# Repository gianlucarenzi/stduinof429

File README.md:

# STDuinoF429
=====================================

First attempt to have an ARDUINO (STM32 Based) Board for usage in 8-bit micros
like Atari 400/800/800XL/130XE and Commodore 64

# Rendered Images
# 
# 
# 

Hardware License
---------------------------
Copyright (C) 2018/2019 Gianluca Renzi <gianlucarenzi@eurek.it> <icjtqr@gmail.com>

The hardware of this project is released as free/open hardware under the
GNU GPL v3 License terms. See LICENSE for details.

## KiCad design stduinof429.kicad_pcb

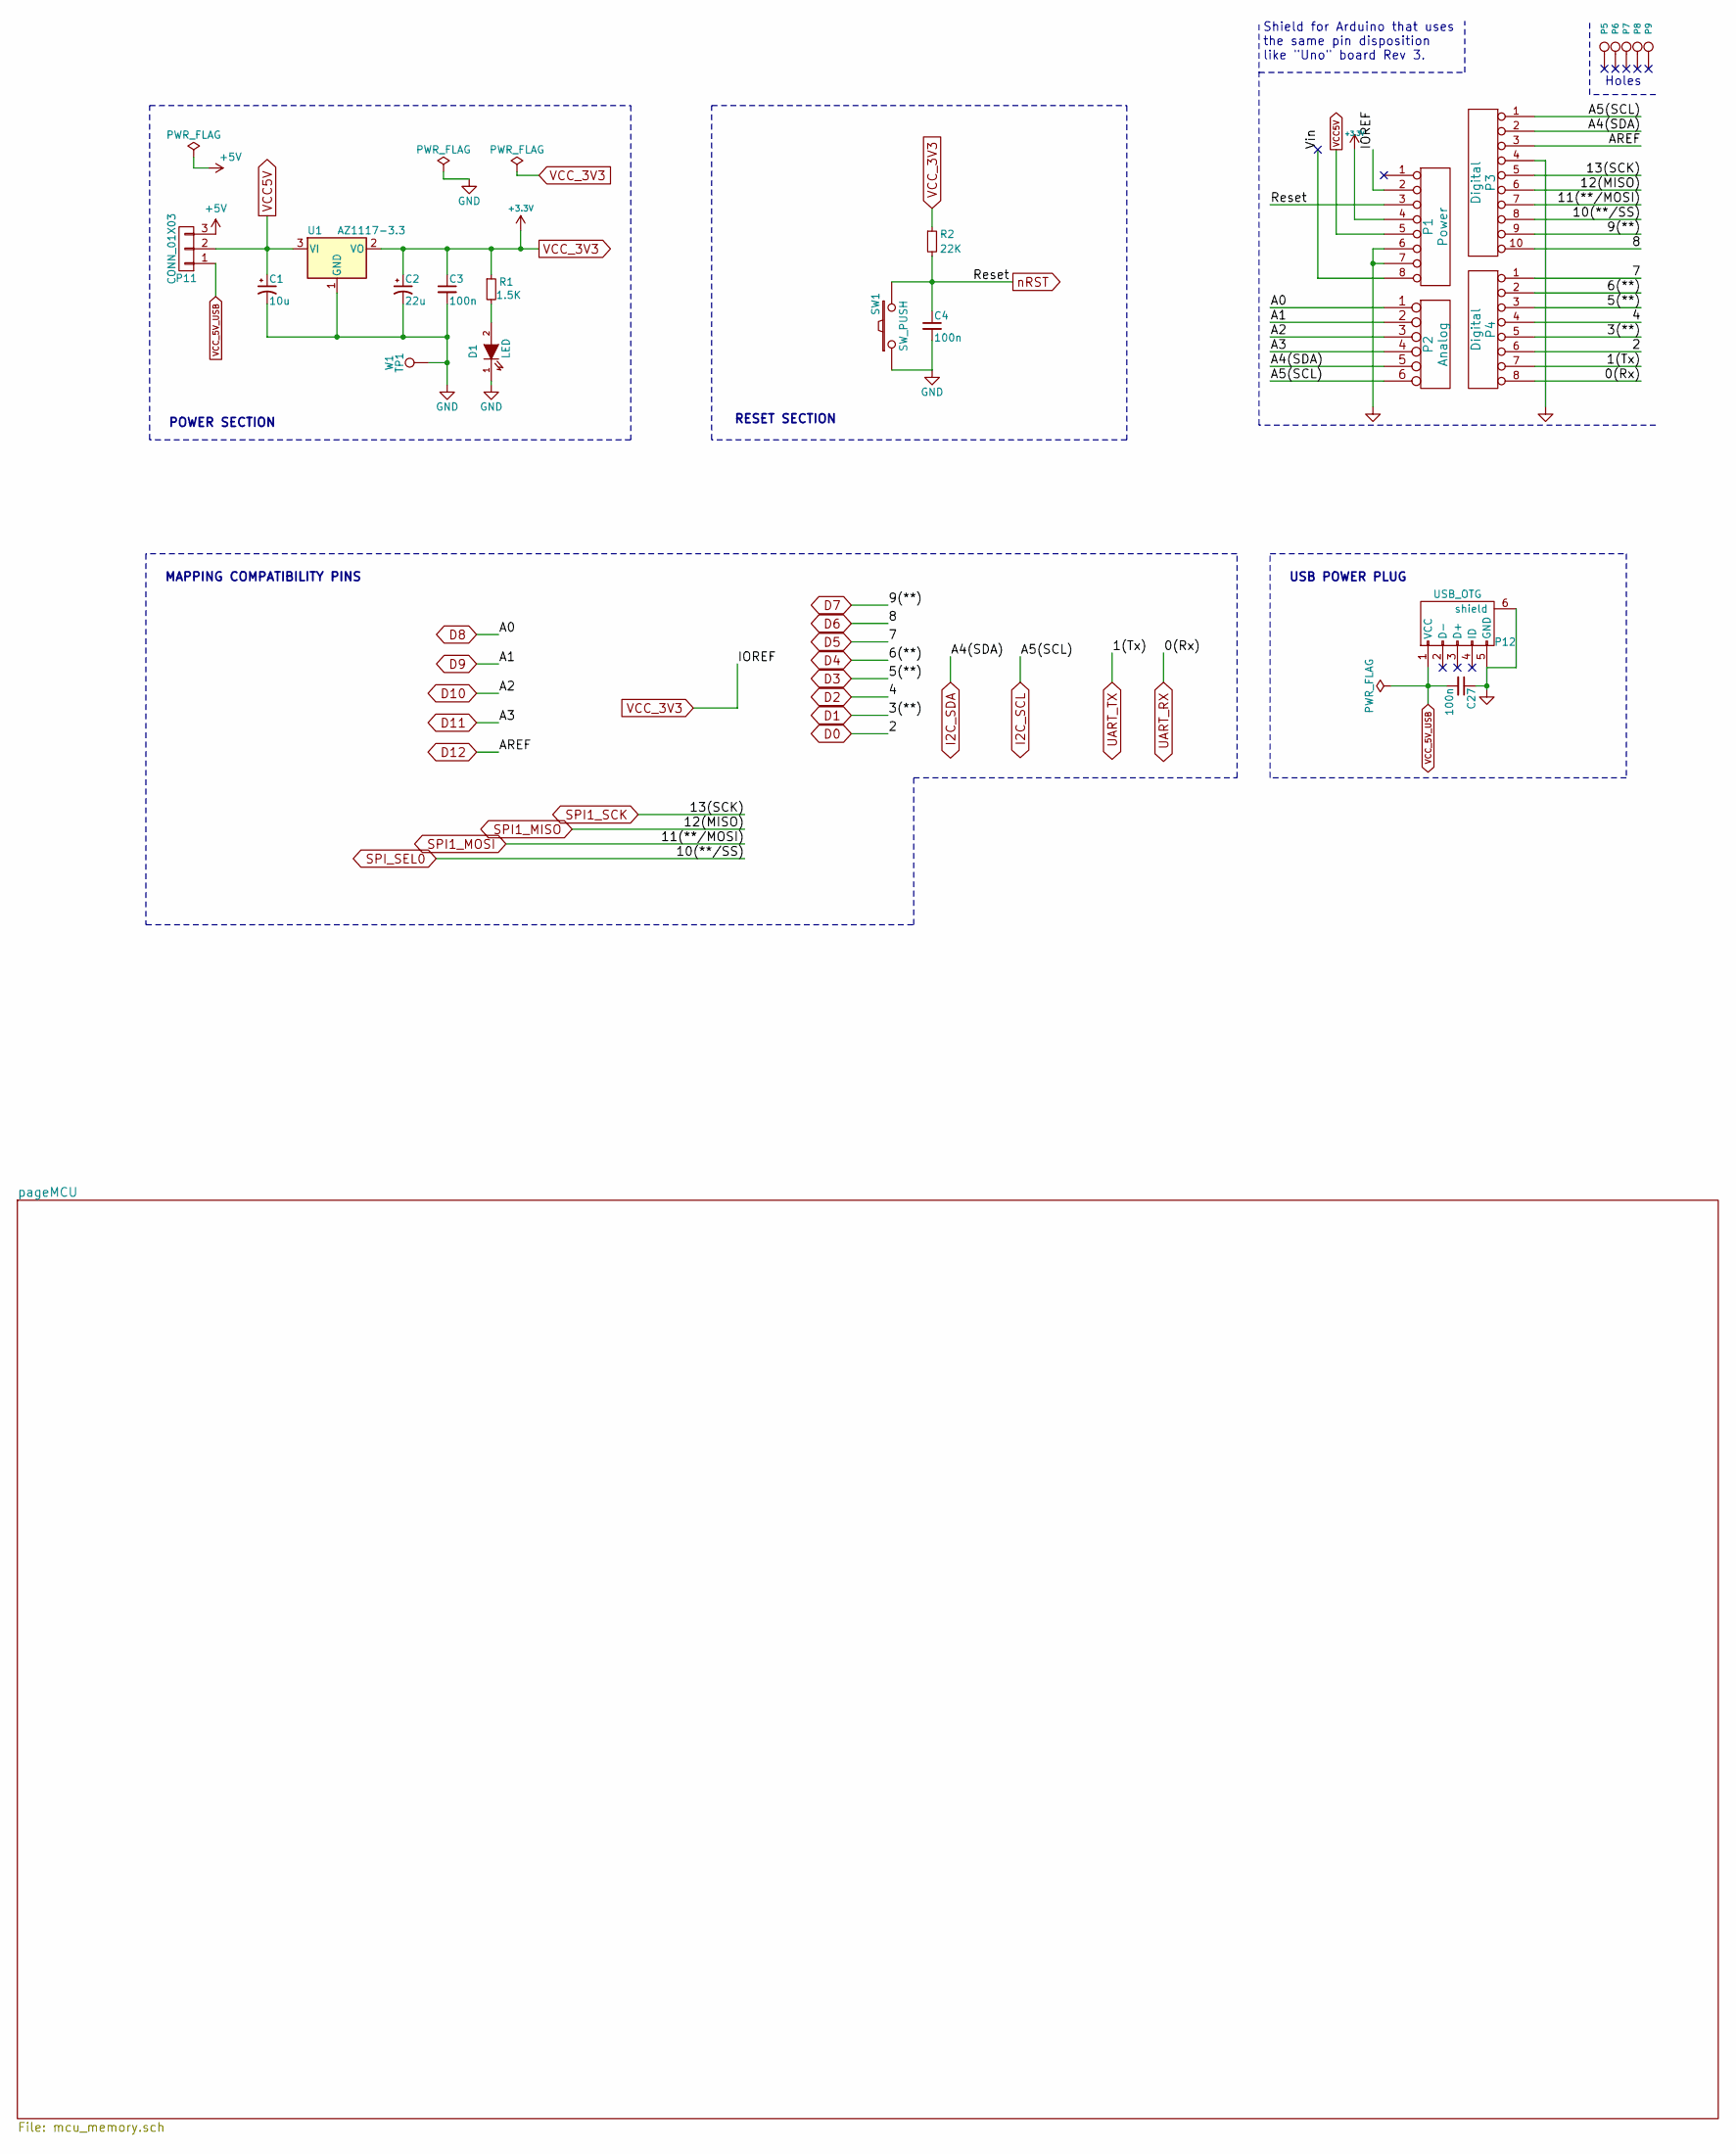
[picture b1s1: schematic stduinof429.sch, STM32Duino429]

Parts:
C1: 10u; CP_EIA-3216-18_Kemet-A_Pad1.58x1.35mm_HandSolder
C2: 22u; CP_EIA-3216-18_Kemet-A_Pad1.58x1.35mm_HandSolder
C3, C4, C27: 100n; C_1210_3225Metric_Pad1.42x2.65mm_HandSolder
D1: LED; LED_1206_3216Metric_Pad1.42x1.75mm_HandSolder
P1: Power; PinSocket_1x08_P2.54mm_Vertical
P2: Analog; PinSocket_1x06_P2.54mm_Vertical
P3: Digital; PinSocket_1x10_P2.54mm_Vertical
P4: Digital; PinSocket_1x08_P2.54mm_Vertical
P5, P6, P7, P8, P9: CONN_1; MountingHole
P11: CONN_01X03; PinHeader_1x03_P2.54mm_Vertical
P12: USB_OTG; USB_Micro-B_Large_Pads
R1: 1.5K; R_1210_3225Metric_Pad1.42x2.65mm_HandSolder
R2: 22K; R_1210_3225Metric_Pad1.42x2.65mm_HandSolder
SW1: SW_PUSH; SW_SPST_FSMSM_3D
U1: AZ1117-3.3; SOT-223
W1: TP1; TestPoint_Pad_D2.0mm

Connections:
+5V: P11.3; also elsewhere on the board
/Vin: P1.8
D0: P4.6; also elsewhere on the board
D1: P4.5; also elsewhere on the board
D2: P4.4; also elsewhere on the board
D3: P4.3; also elsewhere on the board
D4: P4.2; also elsewhere on the board
D5: P4.1; also elsewhere on the board
D6: P3.10; also elsewhere on the board
D7: P3.9; also elsewhere on the board
D8: P2.1; also elsewhere on the board
D9: P2.2; also elsewhere on the board
D10: P2.3; also elsewhere on the board
D11: P2.4; also elsewhere on the board
D12: P3.3; also elsewhere on the board
GND: C1.2, C2.2, C3.2, C4.2, C27.1, D1.1 (K), P1.6, P1.7, P3.4, P12.5 (GND), P12.6 (shield), SW1.1, U1.1 (GND), W1.1; also elsewhere on the board
I2C_SCL: P2.6, P3.1; also elsewhere on the board
I2C_SDA: P2.5, P3.2; also elsewhere on the board
unnamed: D1.2 (A), R1.2
SPI1_MISO: P3.6; also elsewhere on the board
SPI1_MOSI: P3.7; also elsewhere on the board
SPI1_SCK: P3.5; also elsewhere on the board
SPI_SEL0: P3.8; also elsewhere on the board
UART_RX: P4.8; also elsewhere on the board
UART_TX: P4.7; also elsewhere on the board
VCC5V: C1.1, P1.5, P11.2, U1.3 (VI); also elsewhere on the board
VCC_3V3: C2.1, C3.1, P1.2, P1.4, R1.1, R2.1, U1.2 (VO); also elsewhere on the board
VCC_5V_USB: C27.2, P11.1, P12.1 (VCC)
nRST: C4.1, P1.3, R2.2, SW1.2; also elsewhere on the board

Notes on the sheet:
Holes
Shield for Arduino that uses the same pin disposition like "Uno" board Rev 3.
POWER SECTION
MAPPING COMPATIBILITY PINS
RESET SECTION
USB POWER PLUG

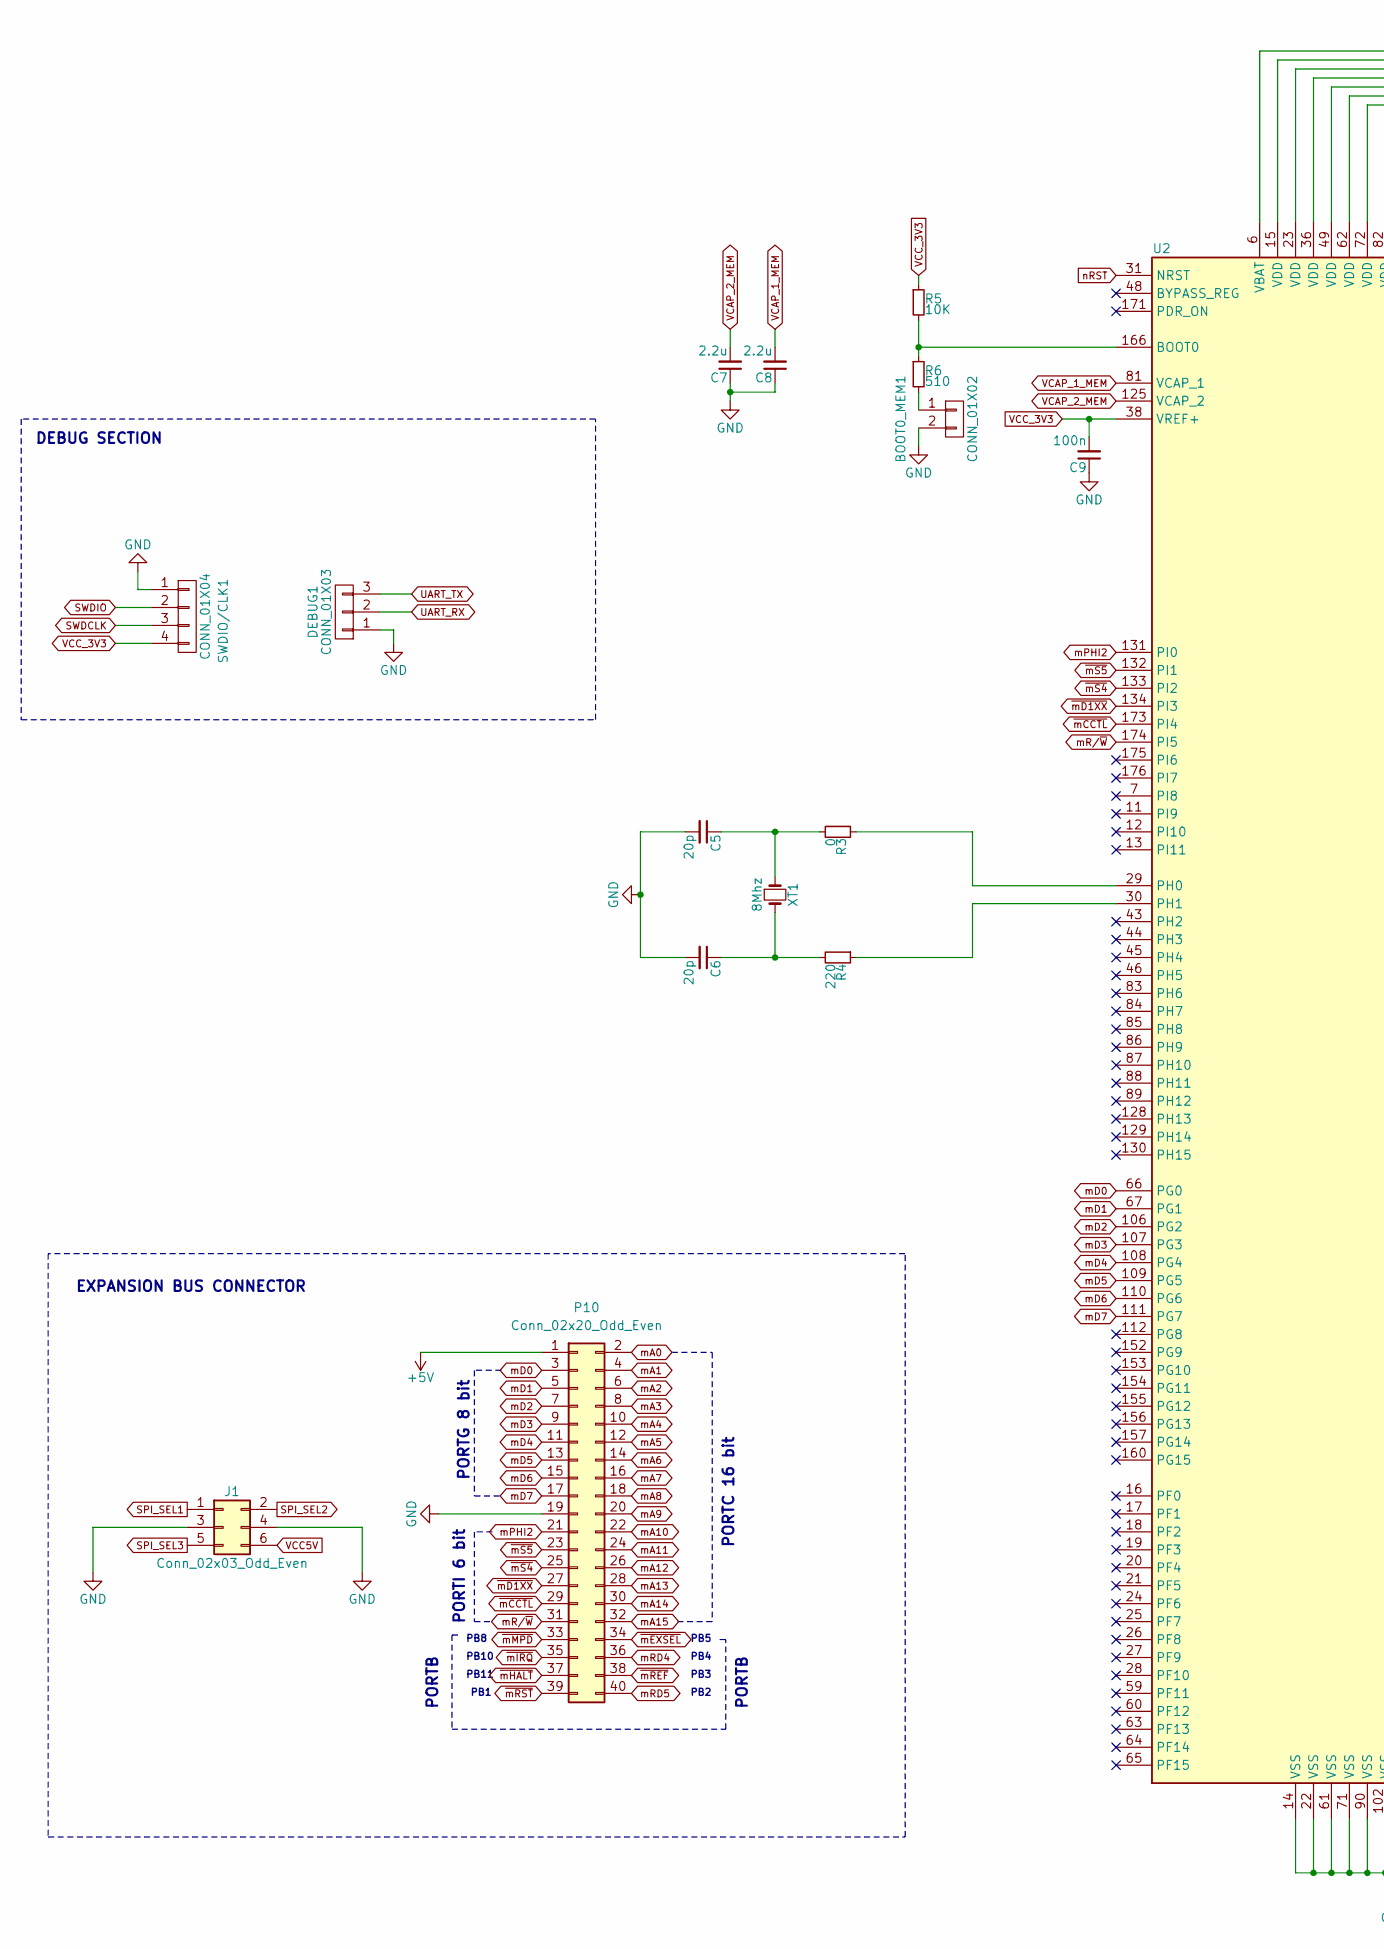
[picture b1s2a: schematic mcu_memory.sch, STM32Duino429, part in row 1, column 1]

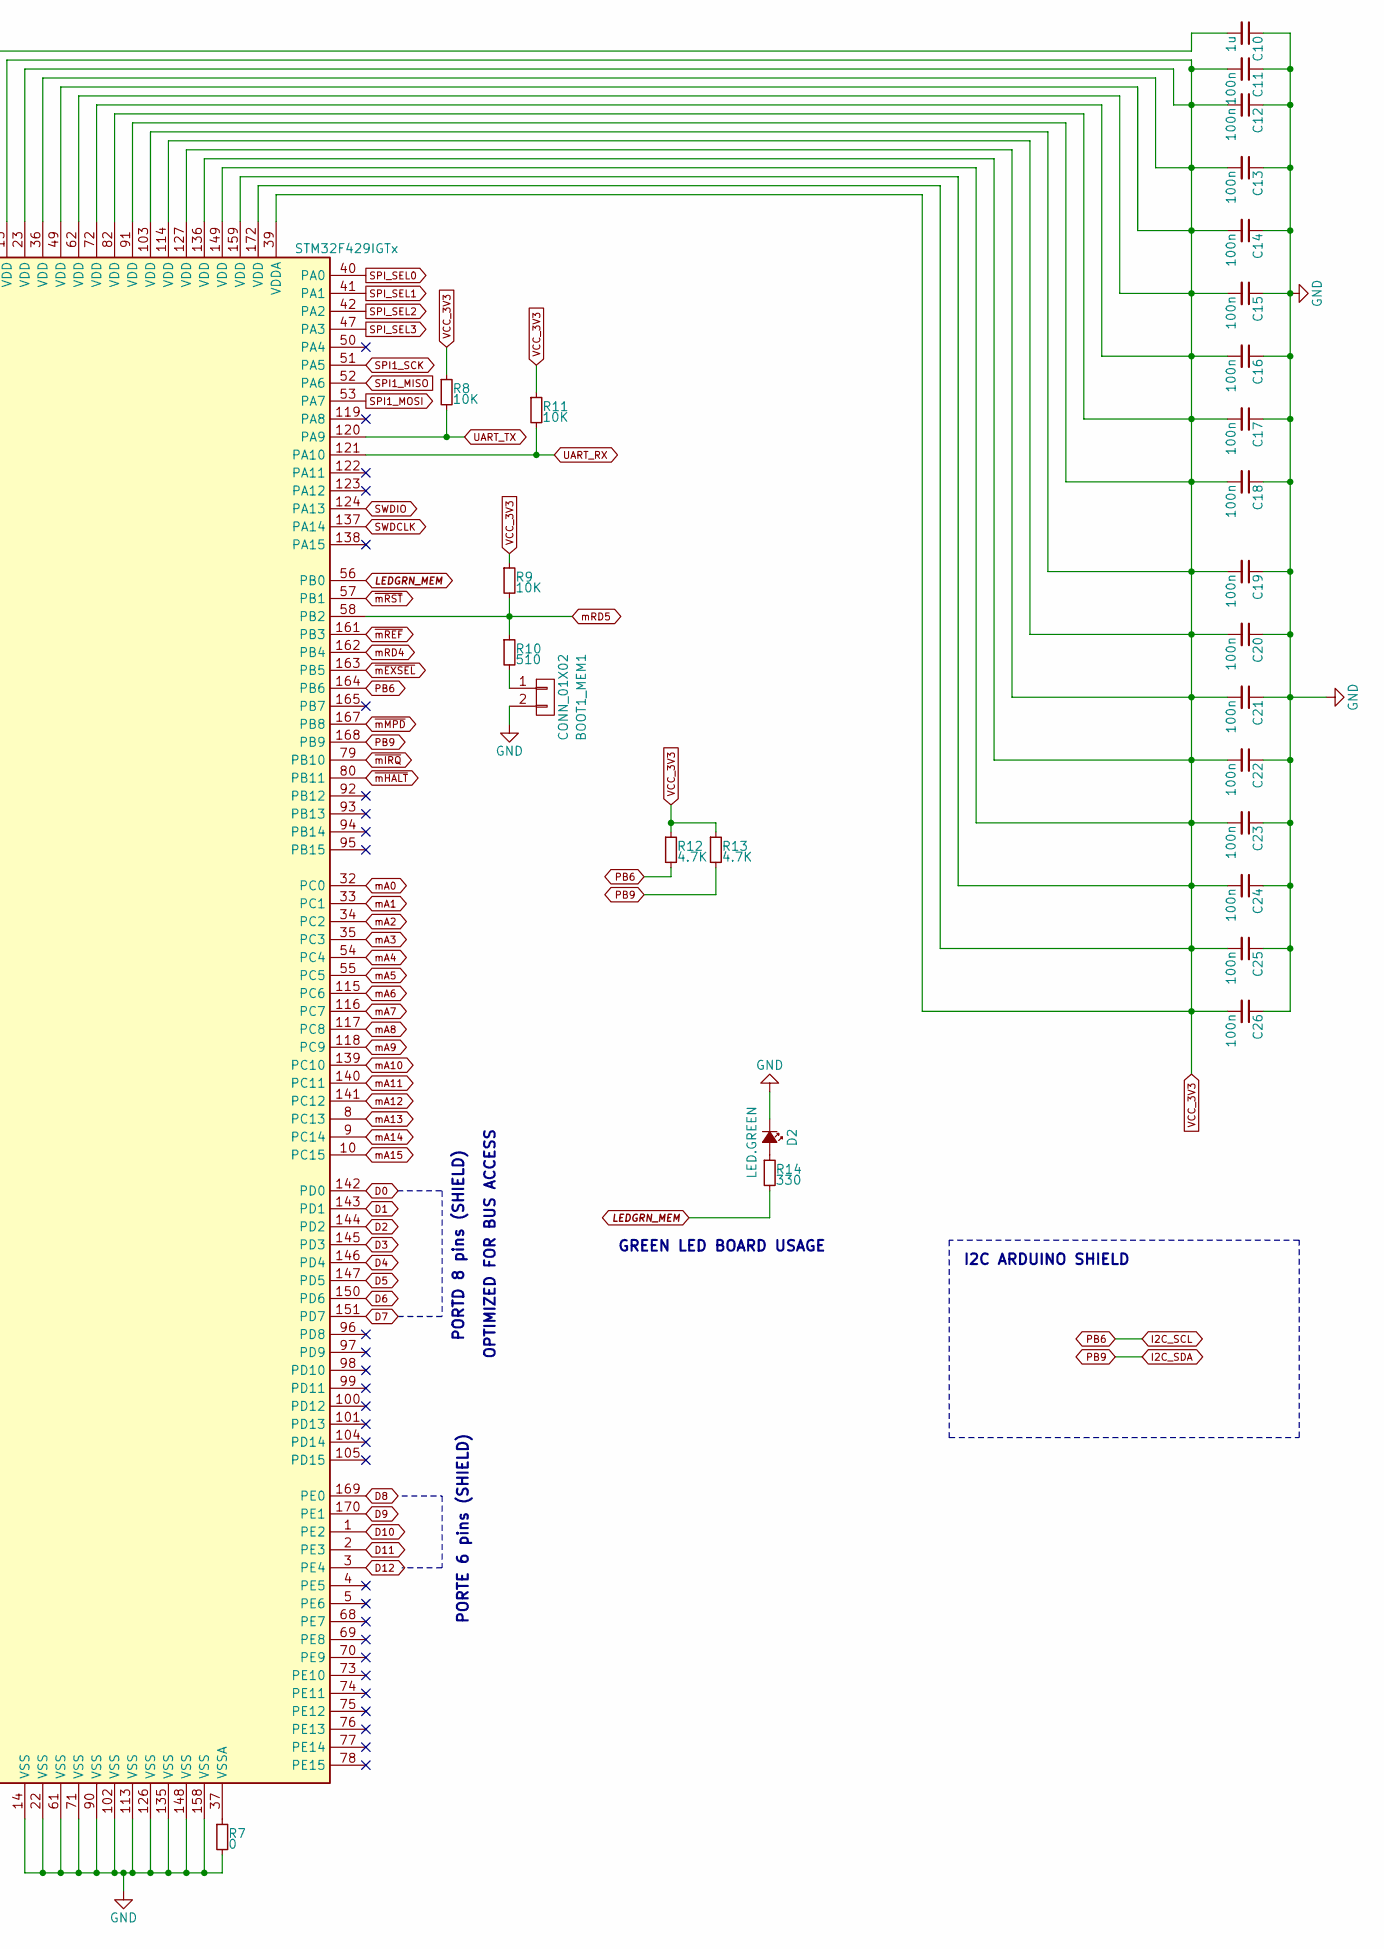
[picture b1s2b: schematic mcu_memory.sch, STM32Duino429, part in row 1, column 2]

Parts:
BOOT0_MEM1, BOOT1_MEM1: CONN_01X02; PinHeader_1x02_P2.54mm_Vertical
C5, C6: 20p; C_1206_3216Metric_Pad1.42x1.75mm_HandSolder
C7, C8: 2.2u; C_1206_3216Metric_Pad1.42x1.75mm_HandSolder
C9, C11, C12, C13, C14, C15, C16, C17, C18, C19, C20, C21, C22, C23, C24, C25, C26: 100n; C_1206_3216Metric_Pad1.42x1.75mm_HandSolder
C10: 1u; C_1206_3216Metric_Pad1.42x1.75mm_HandSolder
D2: LED.GREEN; LED_1206_3216Metric_Pad1.42x1.75mm_HandSolder
DEBUG1: CONN_01X03; PinHeader_1x03_P2.54mm_Vertical
J1: Conn_02x03_Odd_Even; IDC-Header_2x03_P2.54mm_Vertical
P10: Conn_02x20_Odd_Even; IDC_02X20_2.54mm_Horizontal_PCB_2SIDES
R3, R7: 0; R_1206_3216Metric_Pad1.42x1.75mm_HandSolder
R4: 220; R_1206_3216Metric_Pad1.42x1.75mm_HandSolder
R5, R8, R9, R11: 10K; R_1206_3216Metric_Pad1.42x1.75mm_HandSolder
R6, R10: 510; R_1206_3216Metric_Pad1.42x1.75mm_HandSolder
R12, R13: 4.7K; R_1206_3216Metric_Pad1.42x1.75mm_HandSolder
R14: 330; R_1206_3216Metric_Pad1.42x1.75mm_HandSolder
SWDIO/CLK1: CONN_01X04; PinHeader_1x04_P2.54mm_Horizontal
U2: STM32F429IGTx; LQFP-176_24x24mm_P0.5mm
XT1: 8Mhz; Crystal_HC49-4H_Vertical_3D

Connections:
+5V: P10.1; also elsewhere on the board
D0: U2.142 (PD0); also elsewhere on the board
D1: U2.143 (PD1); also elsewhere on the board
D2: U2.144 (PD2); also elsewhere on the board
D3: U2.145 (PD3); also elsewhere on the board
D4: U2.146 (PD4); also elsewhere on the board
D5: U2.147 (PD5); also elsewhere on the board
D6: U2.150 (PD6); also elsewhere on the board
D7: U2.151 (PD7); also elsewhere on the board
D8: U2.169 (PE0); also elsewhere on the board
D9: U2.170 (PE1); also elsewhere on the board
D10: U2.1 (PE2); also elsewhere on the board
D11: U2.2 (PE3); also elsewhere on the board
D12: U2.3 (PE4); also elsewhere on the board
GND: BOOT0_MEM1.2, BOOT1_MEM1.2, C5.2, C6.2, C7.1, C8.1, C9.1, C10.1, C11.1, C12.1, C13.1, C14.1, C15.1, C16.1, C17.1, C18.1, C19.1, C20.1, C21.1, C22.1, C23.1, C24.1, C25.1, C26.1, D2.1 (K), DEBUG1.1, J1.3, J1.4, P10.19, R7.2, SWDIO/CLK1.1, U2.14 (VSS), U2.22 (VSS), U2.61 (VSS), U2.71 (VSS), U2.90 (VSS), U2.102 (VSS), U2.113 (VSS), U2.126 (VSS), U2.135 (VSS), U2.148 (VSS), U2.158 (VSS); also elsewhere on the board
I2C_SCL: R12.2, U2.164 (PB6); also elsewhere on the board
I2C_SDA: R13.2, U2.168 (PB9); also elsewhere on the board
LEDGRN_MEM: R14.2, U2.56 (PB0)
unnamed: BOOT0_MEM1.1, R6.2
unnamed: BOOT1_MEM1.1, R10.2
unnamed: C5.1, R3.2, XT1.1
unnamed: C6.1, R4.2, XT1.2
unnamed: C10.2, U2.6 (VBAT)
unnamed: D2.2 (A), R14.1
unnamed: R3.1, U2.29 (PH0)
unnamed: R4.1, U2.30 (PH1)
unnamed: R5.2, R6.1, U2.166 (BOOT0)
unnamed: R7.1, U2.37 (VSSA)
SPI1_MISO: U2.52 (PA6); also elsewhere on the board
SPI1_MOSI: U2.53 (PA7); also elsewhere on the board
SPI1_SCK: U2.51 (PA5); also elsewhere on the board
SPI_SEL0: U2.40 (PA0); also elsewhere on the board
SPI_SEL1: J1.1, U2.41 (PA1)
SPI_SEL2: J1.2, U2.42 (PA2)
SPI_SEL3: J1.5, U2.47 (PA3)
SWDCLK: SWDIO/CLK1.3, U2.137 (PA14)
SWDIO: SWDIO/CLK1.2, U2.124 (PA13)
UART_RX: DEBUG1.2, R11.2, U2.121 (PA10); also elsewhere on the board
UART_TX: DEBUG1.3, R8.2, U2.120 (PA9); also elsewhere on the board
VCAP_1_MEM: C8.2, U2.81 (VCAP_1)
VCAP_2_MEM: C7.2, U2.125 (VCAP_2)
VCC5V: J1.6; also elsewhere on the board
VCC_3V3: C9.2, C11.2, C12.2, C13.2, C14.2, C15.2, C16.2, C17.2, C18.2, C19.2, C20.2, C21.2, C22.2, C23.2, C24.2, C25.2, C26.2, R5.1, R8.1, R9.1, R11.1, R12.1, R13.1, SWDIO/CLK1.4, U2.15 (VDD), U2.23 (VDD), U2.36 (VDD), U2.38 (VREF+), U2.39 (VDDA), U2.49 (VDD), U2.62 (VDD), U2.72 (VDD), U2.82 (VDD), U2.91 (VDD), U2.103 (VDD), U2.114 (VDD), U2.127 (VDD), U2.136 (VDD), U2.149 (VDD), U2.159 (VDD), U2.172 (VDD); also elsewhere on the board
mA0: P10.2, U2.32 (PC0)
mA1: P10.4, U2.33 (PC1)
mA2: P10.6, U2.34 (PC2)
mA3: P10.8, U2.35 (PC3)
mA4: P10.10, U2.54 (PC4)
mA5: P10.12, U2.55 (PC5)
mA6: P10.14, U2.115 (PC6)
mA7: P10.16, U2.116 (PC7)
mA8: P10.18, U2.117 (PC8)
mA9: P10.20, U2.118 (PC9)
mA10: P10.22, U2.139 (PC10)
mA11: P10.24, U2.140 (PC11)
mA12: P10.26, U2.141 (PC12)
mA13: P10.28, U2.8 (PC13)
mA14: P10.30, U2.9 (PC14)
mA15: P10.32, U2.10 (PC15)
mD0: P10.3, U2.66 (PG0)
mD1: P10.5, U2.67 (PG1)
mD2: P10.7, U2.106 (PG2)
mD3: P10.9, U2.107 (PG3)
mD4: P10.11, U2.108 (PG4)
mD5: P10.13, U2.109 (PG5)
mD6: P10.15, U2.110 (PG6)
mD7: P10.17, U2.111 (PG7)
mPHI2: P10.21, U2.131 (PI0)
mR/~W: P10.31, U2.174 (PI5)
mRD4: P10.36, U2.162 (PB4)
mRD5: P10.40, R9.2, R10.1, U2.58 (PB2)
nRST: U2.31 (NRST); also elsewhere on the board
~mCCTL: P10.29, U2.173 (PI4)
~mD1XX: P10.27, U2.134 (PI3)
~mEXSEL: P10.34, U2.163 (PB5)
~mHALT: P10.37, U2.80 (PB11)
~mIRQ: P10.35, U2.79 (PB10)
~mMPD: P10.33, U2.167 (PB8)
~mREF: P10.38, U2.161 (PB3)
~mRST: P10.39, U2.57 (PB1)
~mS4: P10.25, U2.133 (PI2)
~mS5: P10.23, U2.132 (PI1)

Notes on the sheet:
GREEN LED BOARD USAGE
DEBUG SECTION
EXPANSION BUS CONNECTOR
I2C ARDUINO SHIELD
PORTC 16 bit
PORTG 8 bit
PORTD 8 pins (SHIELD)
PORTI 6 bit
PB8
PB10
PB11
PB1
PB2
PB3
PB4
PB5
PORTB
PORTE 6 pins (SHIELD)
OPTIMIZED FOR BUS ACCESS

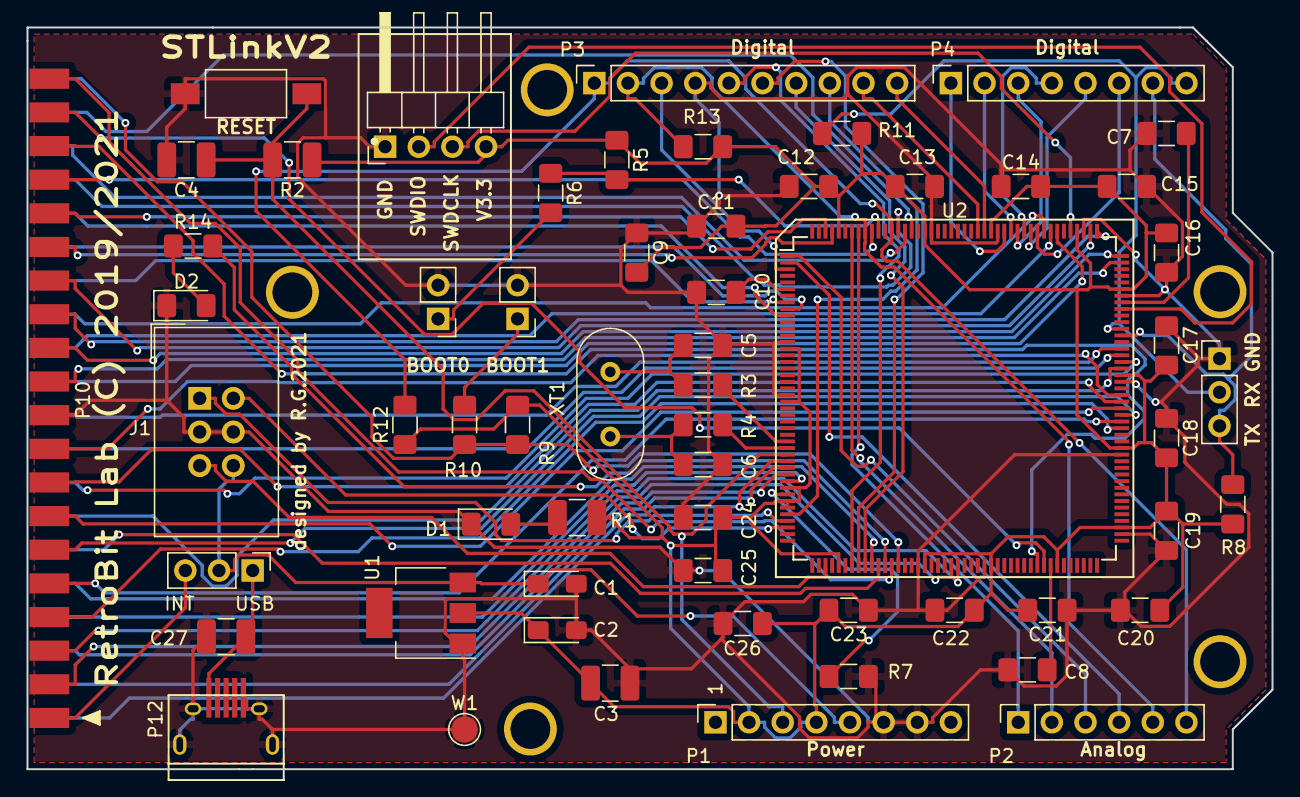
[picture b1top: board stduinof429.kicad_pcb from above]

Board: 2 copper layers, 94.0 x 56.0 mm, 65 parts (0 on the bottom side), 84 nets.

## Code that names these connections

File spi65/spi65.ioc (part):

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Mcu.Name=STM32F429I(E-G)Tx
Mcu.Package=LQFP176
Mcu.UserName=STM32F429IGTx
PA0/WKUP.GPIOParameters=GPIO_Label
PA0/WKUP.GPIO_Label=m_D0
PA0/WKUP.Signal=GPIO_Input
PA1.GPIOParameters=GPIO_Label
PA1.GPIO_Label=m_D1
PA1.Signal=GPIO_Input
PA10.GPIOParameters=GPIO_Label
PA10.GPIO_Label=DEBUG_RX
PA10.Mode=Asynchronous
PA10.Signal=USART1_RX
PA2.GPIOParameters=GPIO_Label
PA2.GPIO_Label=m_D2
PA2.Signal=GPIO_Input
PA3.GPIOParameters=GPIO_Label
PA3.GPIO_Label=m_D3
PA3.Signal=GPIO_Input
PA4.GPIOParameters=GPIO_Label
PA4.GPIO_Label=m_D4
PA4.Signal=GPIO_Input
PA5.GPIOParameters=GPIO_Label
PA5.GPIO_Label=m_D5
PA5.Signal=GPIO_Input
PA6.GPIOParameters=GPIO_Label
PA6.GPIO_Label=m_D6
PA6.Signal=GPIO_Input
PA7.GPIOParameters=GPIO_Label
PA7.GPIO_Label=m_D7
PA7.Signal=GPIO_Input
PA9.GPIOParameters=GPIO_Label
PA9.GPIO_Label=DEBUG_TX
PA9.Mode=Asynchronous
PA9.Signal=USART1_TX
PB0.GPIOParameters=GPIO_Speed,GPIO_Label
PB0.GPIO_Label=LED
PB0.GPIO_Speed=GPIO_SPEED_FREQ_VERY_HIGH
PB0.Signal=GPIO_Output
PB1.GPIOParameters=GPIO_Speed,PinState,GPIO_Label
PB1.GPIO_Label=m_RST
PB1.GPIO_Speed=GPIO_SPEED_FREQ_VERY_HIGH
PB1.PinState=GPIO_PIN_SET
PB1.Signal=GPIO_Output
PB10.GPIOParameters=GPIO_Speed,PinState,GPIO_Label
PB10.GPIO_Label=m_IRQ
PB10.GPIO_Speed=GPIO_SPEED_FREQ_VERY_HIGH
PB10.PinState=GPIO_PIN_SET
PB10.Signal=GPIO_Output
PB2/BOOT1.GPIOParameters=GPIO_Speed,PinState,GPIO_Label
PB2/BOOT1.GPIO_Label=m_RD5
PB2/BOOT1.GPIO_Speed=GPIO_SPEED_FREQ_VERY_HIGH
PB2/BOOT1.PinState=GPIO_PIN_SET
PB2/BOOT1.Signal=GPIO_Output
PB3.GPIOParameters=GPIO_Speed,PinState,GPIO_Label
PB3.GPIO_Label=m_REF
PB3.GPIO_Speed=GPIO_SPEED_FREQ_VERY_HIGH
PB3.PinState=GPIO_PIN_SET
PB3.Signal=GPIO_Output
PB4.GPIOParameters=GPIO_Speed,PinState,GPIO_Label
PB4.GPIO_Label=m_RD4
PB4.GPIO_Speed=GPIO_SPEED_FREQ_VERY_HIGH
PB4.PinState=GPIO_PIN_SET
PB4.Signal=GPIO_Output
PB5.GPIOParameters=GPIO_Speed,PinState,GPIO_Label
PB5.GPIO_Label=m_EXSEL
PB5.GPIO_Speed=GPIO_SPEED_FREQ_VERY_HIGH
PB5.PinState=GPIO_PIN_SET
PB5.Signal=GPIO_Output
PB6.GPIOParameters=GPIO_Speed,GPIO_Label
PB6.GPIO_Label=PB6
PB6.GPIO_Speed=GPIO_SPEED_FREQ_VERY_HIGH
PB6.Signal=GPIO_Output
PB7.GPIOParameters=GPIO_Speed,PinState,GPIO_Label
PB7.GPIO_Label=m_HALT
PB7.GPIO_Speed=GPIO_SPEED_FREQ_VERY_HIGH
PB7.PinState=GPIO_PIN_SET
PB7.Signal=GPIO_Output
PB8.GPIOParameters=GPIO_Speed,PinState,GPIO_Label
PB8.GPIO_Label=m_MPD
PB8.GPIO_Speed=GPIO_SPEED_FREQ_VERY_HIGH
PB8.PinState=GPIO_PIN_SET
PB8.Signal=GPIO_Output
PB9.GPIOParameters=GPIO_Speed,GPIO_Label
PB9.GPIO_Label=PB9
PB9.GPIO_Speed=GPIO_SPEED_FREQ_VERY_HIGH
PB9.Signal=GPIO_Output
PC0.GPIOParameters=GPIO_Label
PC0.GPIO_Label=m_A0
PC0.Signal=GPIO_Input
PC1.GPIOParameters=GPIO_Label
PC1.GPIO_Label=m_A1
PC1.Signal=GPIO_Input
PC10.GPIOParameters=GPIO_Label
PC10.GPIO_Label=m_A10
PC10.Signal=GPIO_Input
PC11.GPIOParameters=GPIO_Label
PC11.GPIO_Label=m_A11
PC11.Signal=GPIO_Input
PC12.GPIOParameters=GPIO_Label
PC12.GPIO_Label=m_A12
PC12.Signal=GPIO_Input
PC13.GPIOParameters=GPIO_Label
PC13.GPIO_Label=m_A13
PC13.Signal=GPIO_Input
PC14/OSC32_IN.GPIOParameters=GPIO_Label
PC14/OSC32_IN.GPIO_Label=m_A14
PC14/OSC32_IN.Signal=GPIO_Input
PC15/OSC32_OUT.GPIOParameters=GPIO_Label
PC15/OSC32_OUT.GPIO_Label=m_A15
PC15/OSC32_OUT.Signal=GPIO_Input
PC2.GPIOParameters=GPIO_Label
PC2.GPIO_Label=m_A2
PC2.Signal=GPIO_Input
PC3.GPIOParameters=GPIO_Label
PC3.GPIO_Label=m_A3
PC3.Signal=GPIO_Input
PC4.GPIOParameters=GPIO_Label
PC4.GPIO_Label=m_A4
PC4.Signal=GPIO_Input
PC5.GPIOParameters=GPIO_Label
PC5.GPIO_Label=m_A5
PC5.Signal=GPIO_Input
PC6.GPIOParameters=GPIO_Label
PC6.GPIO_Label=m_A6
PC6.Signal=GPIO_Input
PC7.GPIOParameters=GPIO_Label
PC7.GPIO_Label=m_A7
PC7.Signal=GPIO_Input
PC8.GPIOParameters=GPIO_Label
PC8.GPIO_Label=m_A8
PC8.Signal=GPIO_Input
PC9.GPIOParameters=GPIO_Label
PC9.GPIO_Label=m_A9
PC9.Signal=GPIO_Input
PD0.Signal=FMC_D2_DA2
PD1.Signal=FMC_D3_DA3
PD11.Signal=FMC_A16_CLE
PD12.Signal=FMC_A17_ALE
PD13.Signal=FMC_A18
PD14.Signal=FMC_D0_DA0
PD15.Signal=FMC_D1_DA1
PD4.Signal=FMC_NOE
PD5.Signal=FMC_NWE
PD7.Mode=NorPsramChipSelect1_1
PD7.Signal=FMC_NE1
PE10.Signal=FMC_D7_DA7
PE3.Signal=FMC_A19
PE7.Signal=FMC_D4_DA4
PE8.Signal=FMC_D5_DA5
PE9.Signal=FMC_D6_DA6
PF0.Signal=FMC_A0
PF1.Signal=FMC_A1
PF12.Signal=FMC_A6
PF13.Signal=FMC_A7
PF14.Signal=FMC_A8
PF15.Signal=FMC_A9
PF2.Signal=FMC_A2
PF3.Signal=FMC_A3
PF4.Signal=FMC_A4
PF5.Signal=FMC_A5
PG0.Signal=FMC_A10
PG1.Signal=FMC_A11
PG2.Signal=FMC_A12
PG3.Signal=FMC_A13
PG4.Signal=FMC_A14_BA0
PG5.Signal=FMC_A15_BA1
PH0/OSC_IN.Mode=HSE-External-Clock-Source
PH0/OSC_IN.Signal=RCC_OSC_IN
PH1/OSC_OUT.Mode=HSE-External-Clock-Source
PH1/OSC_OUT.Signal=RCC_OSC_OUT
PI0.GPIOParameters=GPIO_Label
PI0.GPIO_Label=m_PHI2
PI0.Signal=GPIO_Input
PI1.GPIOParameters=GPIO_Label
PI1.GPIO_Label=m_S5
PI1.Signal=GPIO_Input
PI2.GPIOParameters=GPIO_Label
PI2.GPIO_Label=m_S4
PI2.Signal=GPIO_Input
PI3.GPIOParameters=GPIO_Label
PI3.GPIO_Label=m_D1XX
PI3.Signal=GPIO_Input
PI4.GPIOParameters=GPIO_Label
PI4.GPIO_Label=m_CCTL
PI4.Signal=GPIO_Input
PI5.GPIOParameters=GPIO_Label
PI5.GPIO_Label=m_RW
PI5.Signal=GPIO_Input
PI6.GPIOParameters=GPIO_Label
PI6.GPIO_Label=CONF0
PI6.Signal=GPIO_Input
PI7.GPIOParameters=GPIO_Label
PI7.GPIO_Label=CONF1
PI7.Signal=GPIO_Input
PI8.GPIOParameters=GPIO_Label
PI8.GPIO_Label=CONF2
PI8.Signal=GPIO_Input
RCC.HSE_VALUE=8000000
RCC.SYSCLKFreq_VALUE=180000000
RCC.SYSCLKSource=RCC_SYSCLKSOURCE_PLLCLK
board=custom

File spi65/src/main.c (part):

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#define CPU_RESET_ASSERT      LL_GPIO_ResetOutputPin(GPIOB, GPIO_PIN_1); /* RST -> GPIO(B.1) LOW */
#define CPU_RESET_DEASSERT    LL_GPIO_SetOutputPin(GPIOB, GPIO_PIN_1);   /* RST -> GPIO(B.1) HIGH */

#define SPI_SLAVE_SELECT(a)   LL_GPIO_ResetOutputPin(GPIOA, (1 << a)); /* PA0-PA1-PA2-PA3 */

static volatile uint8_t SPI_DATA_IN;
static volatile uint8_t SPI_DATA_OUT;
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	reg = 0xD500;
	*(reg + 1) = 3; // setup CPOL and CPHA
	*(reg + 2) = 2; // store DIV8 CLK divisor
	*(reg + 3) = 1; // setup SLAVE #1 SPI_SEL0

	for (x = 0; x < strlen(char); x++)
	{
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
	LL_AHB1_GRP1_EnableClock(LL_AHB1_GRP1_PERIPH_GPIOA);
	/**USART1 GPIO Configuration
	PA9   ------> USART1_TX
	PA10   ------> USART1_RX
	*/
	GPIO_InitStruct.Pin = DEBUG_TX_Pin|DEBUG_RX_Pin;
	GPIO_InitStruct.Mode = LL_GPIO_MODE_ALTERNATE;
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	LL_AHB1_GRP1_EnableClock(LL_AHB1_GRP1_PERIPH_GPIOD);

	/* Low level by default */
	LL_GPIO_ResetOutputPin(GPIOB, LED_Pin | PB6_Pin | PB9_Pin);

	/* ------------------------
	 * CONTROL SIGNALS TO 6502
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		m_RD4_Pin  | m_EXSEL_Pin | m_HALT_Pin  | m_MPD_Pin;

	/* Miscellaneous pins for STM32F4 bootup */
	GPIO_InitStruct.Pin |= PB6_Pin | PB9_Pin;

	GPIO_InitStruct.Mode = LL_GPIO_MODE_OUTPUT;
	GPIO_InitStruct.Speed = LL_GPIO_SPEED_FREQ_VERY_HIGH;
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	GPIO_InitStruct.Speed = LL_GPIO_SPEED_FREQ_VERY_HIGH;
	GPIO_InitStruct.OutputType = LL_GPIO_OUTPUT_PUSHPULL;
	GPIO_InitStruct.Pull = LL_GPIO_PULL_UP; /* All devices start deselected */
	LL_GPIO_Init(SPI_SEL0_GPIO_Port, &GPIO_InitStruct);
}


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	LL_APB2_GRP1_EnableClock(LL_APB2_GRP1_PERIPH_SPI1);

	/* SPI1 GPIO Config */
	GPIO_InitStruct.Pin = SPI1_MISO_Pin | SPI1_MOSI_Pin | SPI1_SCK_Pin;
	GPIO_InitStruct.Mode = LL_GPIO_MODE_ALTERNATE;
	GPIO_InitStruct.Speed = LL_GPIO_SPEED_FREQ_VERY_HIGH;
	GPIO_InitStruct.OutputType = LL_GPIO_OUTPUT_PUSHPULL;
	GPIO_InitStruct.Pull = LL_GPIO_PULL_NO;
	GPIO_InitStruct.Alternate = LL_GPIO_AF_5;
	LL_GPIO_Init(SPI1_MISO_Port, &GPIO_InitStruct);

	/* SPI Core Config */
	SPI_InitStruct.TransferDirection = LL_SPI_FULL_DUPLEX;
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
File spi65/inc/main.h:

/* USER CODE BEGIN Header */
/**
  ******************************************************************************
  * @file           : main.h
  * @brief          : Header for main.c file.
  *                   This file contains the common defines of the application.
  ******************************************************************************
  * @attention
  *
  * <h2><center>&copy; Copyright (c) 2019 STMicroelectronics.
  * All rights reserved.</center></h2>
  *
  * This software component is licensed by ST under BSD 3-Clause license,
  * the "License"; You may not use this file except in compliance with the
  * License. You may obtain a copy of the License at:
  *                        opensource.org/licenses/BSD-3-Clause
  *
  ******************************************************************************
  */
/* USER CODE END Header */

/* Define to prevent recursive inclusion -------------------------------------*/
#ifndef __MAIN_H
#define __MAIN_H

#ifdef __cplusplus
extern "C" {
#endif

/* Includes ------------------------------------------------------------------*/
#include "stm32f4xx_hal.h"
#include "stm32f4xx_hal.h"
#include "stm32f4xx_ll_rcc.h"
#include "stm32f4xx_ll_bus.h"
#include "stm32f4xx_ll_system.h"
#include "stm32f4xx_ll_exti.h"
#include "stm32f4xx_ll_cortex.h"
#include "stm32f4xx_ll_utils.h"
#include "stm32f4xx_ll_pwr.h"
#include "stm32f4xx_ll_dma.h"
#include "stm32f4xx_ll_usart.h"
#include "stm32f4xx.h"
#include "stm32f4xx_ll_gpio.h"
#include "stm32f4xx_ll_spi.h"

extern void Error_Handler(const char *c);

/* ADDRESS BUS PINS 16BIT */
#define m_A15_Pin LL_GPIO_PIN_15
#define m_A15_GPIO_Port GPIOC
#define m_A14_Pin LL_GPIO_PIN_14
#define m_A14_GPIO_Port GPIOC
#define m_A13_Pin LL_GPIO_PIN_13
#define m_A13_GPIO_Port GPIOC
#define m_A12_Pin LL_GPIO_PIN_12
#define m_A12_GPIO_Port GPIOC
#define m_A11_Pin LL_GPIO_PIN_11
#define m_A11_GPIO_Port GPIOC
#define m_A10_Pin LL_GPIO_PIN_10
#define m_A10_GPIO_Port GPIOC
#define m_A9_Pin LL_GPIO_PIN_9
#define m_A9_GPIO_Port GPIOC
#define m_A8_Pin LL_GPIO_PIN_8
#define m_A8_GPIO_Port GPIOC
#define m_A7_Pin LL_GPIO_PIN_7
#define m_A7_GPIO_Port GPIOC
#define m_A6_Pin LL_GPIO_PIN_6
#define m_A6_GPIO_Port GPIOC
#define m_A5_Pin LL_GPIO_PIN_5
#define m_A5_GPIO_Port GPIOC
#define m_A4_Pin LL_GPIO_PIN_4
#define m_A4_GPIO_Port GPIOC
#define m_A3_Pin LL_GPIO_PIN_3
#define m_A3_GPIO_Port GPIOC
#define m_A2_Pin LL_GPIO_PIN_2
#define m_A2_GPIO_Port GPIOC
#define m_A1_Pin LL_GPIO_PIN_1
#define m_A1_GPIO_Port GPIOC
#define m_A0_Pin LL_GPIO_PIN_0
#define m_A0_GPIO_Port GPIOC

/* DATA BUS 8BIT */
#define m_D0_Pin LL_GPIO_PIN_0
#define m_D0_GPIO_Port GPIOG
#define m_D1_Pin LL_GPIO_PIN_1
#define m_D1_GPIO_Port GPIOG
#define m_D2_Pin LL_GPIO_PIN_2
#define m_D2_GPIO_Port GPIOG
#define m_D3_Pin LL_GPIO_PIN_3
#define m_D3_GPIO_Port GPIOG
#define m_D4_Pin LL_GPIO_PIN_4
#define m_D4_GPIO_Port GPIOG
#define m_D5_Pin LL_GPIO_PIN_5
#define m_D5_GPIO_Port GPIOG
#define m_D6_Pin LL_GPIO_PIN_6
#define m_D6_GPIO_Port GPIOG
#define m_D7_Pin LL_GPIO_PIN_7
#define m_D7_GPIO_Port GPIOG

/* LED */
#define LED_Pin LL_GPIO_PIN_0
#define LED_GPIO_Port GPIOB

/* CONTROL TO 6502 RESET,RD5,RD4,... */
#define m_RST_Pin LL_GPIO_PIN_1
#define m_RST_GPIO_Port GPIOB
#define m_RD5_Pin LL_GPIO_PIN_2
#define m_RD5_GPIO_Port GPIOB
//#define m_REF_Pin LL_GPIO_PIN_3
//#define m_REF_GPIO_Port GPIOB
#define m_RD4_Pin LL_GPIO_PIN_4
#define m_RD4_GPIO_Port GPIOB
#define m_EXSEL_Pin LL_GPIO_PIN_5
#define m_EXSEL_GPIO_Port GPIOB
#define PB6_Pin LL_GPIO_PIN_6
#define PB6_GPIO_Port GPIOB
#define m_HALT_Pin LL_GPIO_PIN_7
#define m_HALT_GPIO_Port GPIOB
#define m_MPD_Pin LL_GPIO_PIN_8
#define m_MPD_GPIO_Port GPIOB
#define PB9_Pin LL_GPIO_PIN_9
#define PB9_GPIO_Port GPIOB
#define m_IRQ_Pin LL_GPIO_PIN_10
#define m_IRQ_GPIO_Port GPIOB

/* CONTROL FROM 6502 PHI2 CLK, R/W, ... */
#define m_PHI2_Pin LL_GPIO_PIN_0
#define m_PHI2_GPIO_Port GPIOI
#define m_S5_Pin LL_GPIO_PIN_1
#define m_S5_GPIO_Port GPIOI
#define m_S4_Pin LL_GPIO_PIN_2
#define m_S4_GPIO_Port GPIOI
#define m_D1XX_Pin LL_GPIO_PIN_3
#define m_D1XX_GPIO_Port GPIOI
#define m_CCTL_Pin LL_GPIO_PIN_4
#define m_CCTL_GPIO_Port GPIOI
#define m_RW_Pin LL_GPIO_PIN_5
#define m_RW_GPIO_Port GPIOI
#define m_IO1_Pin LL_GPIO_PIN_9
#define m_IO1_GPIO_Port GPIOI
#define m_IO2_Pin LL_GPIO_PIN_10
#define m_IO2_GPIO_Port GPIOI

/* DEBUG UART */
#define DEBUG_TX_Pin LL_GPIO_PIN_9
#define DEBUG_TX_GPIO_Port GPIOA
#define DEBUG_RX_Pin LL_GPIO_PIN_10
#define DEBUG_RX_GPIO_Port GPIOA

/* EMULATION Configuration PIN */
#define CONF0_Pin LL_GPIO_PIN_6
#define CONF0_GPIO_Port GPIOI
#define CONF1_Pin LL_GPIO_PIN_7
#define CONF1_GPIO_Port GPIOI
#define CONF2_Pin LL_GPIO_PIN_8
#define CONF2_GPIO_Port GPIOI

/* SPI PINS */
#define SPI1_MISO_Port GPIOA
#define SPI1_MISO_Pin LL_GPIO_PIN_6
#define SPI1_SCK_Port GPIOA
#define SPI1_SCK_Pin LL_GPIO_PIN_5
#define SPI1_MOSI_Port GPIOA
#define SPI1_MOSI_Pin LL_GPIO_PIN_7

/* SPI CHIP SELECT */
#define SPI_SEL0_GPIO_Pin  LL_GPIO_PIN_0
#define SPI_SEL0_GPIO_Port GPIOA
#define SPI_SEL1_GPIO_Pin  LL_GPIO_PIN_1
#define SPI_SEL1_GPIO_Port GPIOA
#define SPI_SEL2_GPIO_Pin  LL_GPIO_PIN_2
#define SPI_SEL2_GPIO_Port GPIOA
#define SPI_SEL3_GPIO_Pin  LL_GPIO_PIN_3
#define SPI_SEL3_GPIO_Port GPIOA

#ifdef __cplusplus
}
#endif

#endif /* __MAIN_H */

/************************ (C) COPYRIGHT STMicroelectronics *****END OF FILE****/

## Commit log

2019-10-13 First Import
2019-10-13 Added README
2019-10-14 Corrected pinout of lateral IDC 40 pin. Moved other bits to another port
2019-10-14 - Corrected the PBI Device # read on address bus (was 0x0F instead of 0xFF) - SPI_ENABLED is invoked __before__ running the main loop if __no__ ATARI_PBI_DEVICE is defined
2019-10-19 Rerouted with signals (address and data bus) with length match
2019-10-19 Rerouting with length match
2019-10-22 digikey
2019-11-01 Updated. Ready to be ordered
2019-11-01 Sent to JLCPCB
2019-11-02 Modified using the Digikey codes
2019-11-25 Added BillOfMaterial from Digikey in XLSX format
2019-11-25 Better layout
2020-05-23 Porting from Kicad 4 to Kicad 5
2020-05-23 Rigenerato PDF
2021-03-22 Removed. Not needed anymore
2021-03-22 Added
2021-03-22 Added without the packages/kicad folder needed. All stuff is now on kicad sources and RetroBitLab Library
2021-03-22 Modified for Kicad 5.1.9
2021-03-25 Created for rescue :-(
2025-11-01 RetroBitLab library

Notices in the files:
stduinof429.kicad_pcb:
RetroBit Lab (C) 2019/2021
